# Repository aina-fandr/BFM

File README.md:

# Projet AGV bancaire — BFM V4

Bienvenue dans le dépôt du projet AGV bancaire. Cette page regroupe les liens vers les présentations, les livrables principaux et les dossiers de travail.

## Présentations et livrables principaux

- **[Présentation aux investisseurs — version HTML](<LIVRABLES FINAUX/Dossier de financement/Presentation_investisseurs_AGV_GARP_c.html>)**
- [Dossier de financement — version PDF](<LIVRABLES FINAUX/Dossier de financement/Dossier_financement_AGV.pdf>)
- [Dossier de financement — version HTML](<LIVRABLES FINAUX/Dossier de financement/Dossier_financement_AGV.html>)
- [Présentation visuelle interactive BFM V4](<LIVRABLES FINAUX/Dossier de Conception Final/BFM_V4_GITHUB/index.html>) — modèles 3D, plans et ressources associés
- [Atlas 2D BFM V4](<LIVRABLES FINAUX/Dossier de financement/Atlas_2D_BFM_V4.html>)
- [Simulation AGV hors ligne](<LIVRABLES FINAUX/Dossier de financement/Simulation_AGV_hors_ligne.html>)
- [Étude de la carte électronique](<LIVRABLES FINAUX/Dossier de financement/Etude_PCB_AGV.html>)
- [État des dossiers livrables](<LIVRABLES FINAUX/ETAT_DES_DOSSIERS.md>)

> GitHub affiche parfois les fichiers HTML comme du code dans le dépôt. Pour ouvrir les présentations HTML comme des pages web, activez GitHub Pages dans les paramètres du dépôt. La présentation BFM V4 doit être publiée avec son dossier `assets`.

## Dossiers du projet

| Domaine | Contenu |
|---|---|
| [Approvisionnement](<APPROVISIONNEMENT/README.md>) | Nomenclatures, budgets et achats |
| [Coordination du projet](<COORDINATION DU PROJET/README.md>) | Équipe, réunions et suivi |
| [Électronique](<ELECTRONIQUE/README.md>) | Architecture, alimentation et câblage |
| [Informatique](<INFORMATIQUE/README.md>) | Logiciel, communication et firmware |
| [Livrables finaux](<LIVRABLES FINAUX/README.md>) | Dossiers de conception, fabrication et validation |
| [Mécanique](<MECANIQUE/README.md>) | Études, calculs et modélisation |
| [Qualité et sécurité](<QUALITE ET SECURITE/README.md>) | Risques, normes et validation |
| [Robotique](<ROBOTIQUE/README.md>) | Architecture, cartographie et simulation |
| [Outils](<outils/README.md>) | Scripts et génération de documentation |

## Documentation

- [Avancement du projet](<AVANCEMENT_PROJET.md>)
- [Synthèse détaillée du projet](<README_PROJET.md>)
- [Guide des registres](<README_REGISTRES.md>)
- [Structure complète des fichiers](<STRUCTURE_COMPLETE.md>)

Les modèles, budgets et simulations sont des éléments de conception ou des estimations. Ils ne constituent pas une validation de fabrication, de sécurité ou de performance réelle.

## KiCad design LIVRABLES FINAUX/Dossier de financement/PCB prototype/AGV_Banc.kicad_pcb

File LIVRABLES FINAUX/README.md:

# LIVRABLES FINAUX

Regroupe les dossiers de conception, fabrication, electronique, informatique, robotique, qualite, rapports et validations.

## Contenu du dossier

- [Cahier Des Charges Final/](<Cahier Des Charges Final/>)
- [Dossier de Conception Final/](<Dossier de Conception Final/>)
- [Dossier de Fabrication/](<Dossier de Fabrication/>)
- [Dossier Electrique Final/](<Dossier Electrique Final/>)
- [Dossier Informatique/](<Dossier Informatique/>)
- [Dossier Qualité et Securité/](<Dossier Qualité et Securité/>)
- [Dossier Robotique/](<Dossier Robotique/>)
- [Rapport Final du Projet/](<Rapport Final du Projet/>)
- [Rapports Tests et Validation/](<Rapports Tests et Validation/>)

Fichiers directement presents a la racine :
- `ETAT_DES_DOSSIERS.md`

## Structure complete

Voir [STRUCTURE_COMPLETE.md](<STRUCTURE_COMPLETE.md>) pour l'arborescence detaillee de ce dossier et de ses sous-dossiers.

## Mise a jour

Depuis la racine `PROJET BANQUE CENTRALE`, regenerer les structures avec :

```powershell
python .\outils\generer_documentation_dossiers.py
```

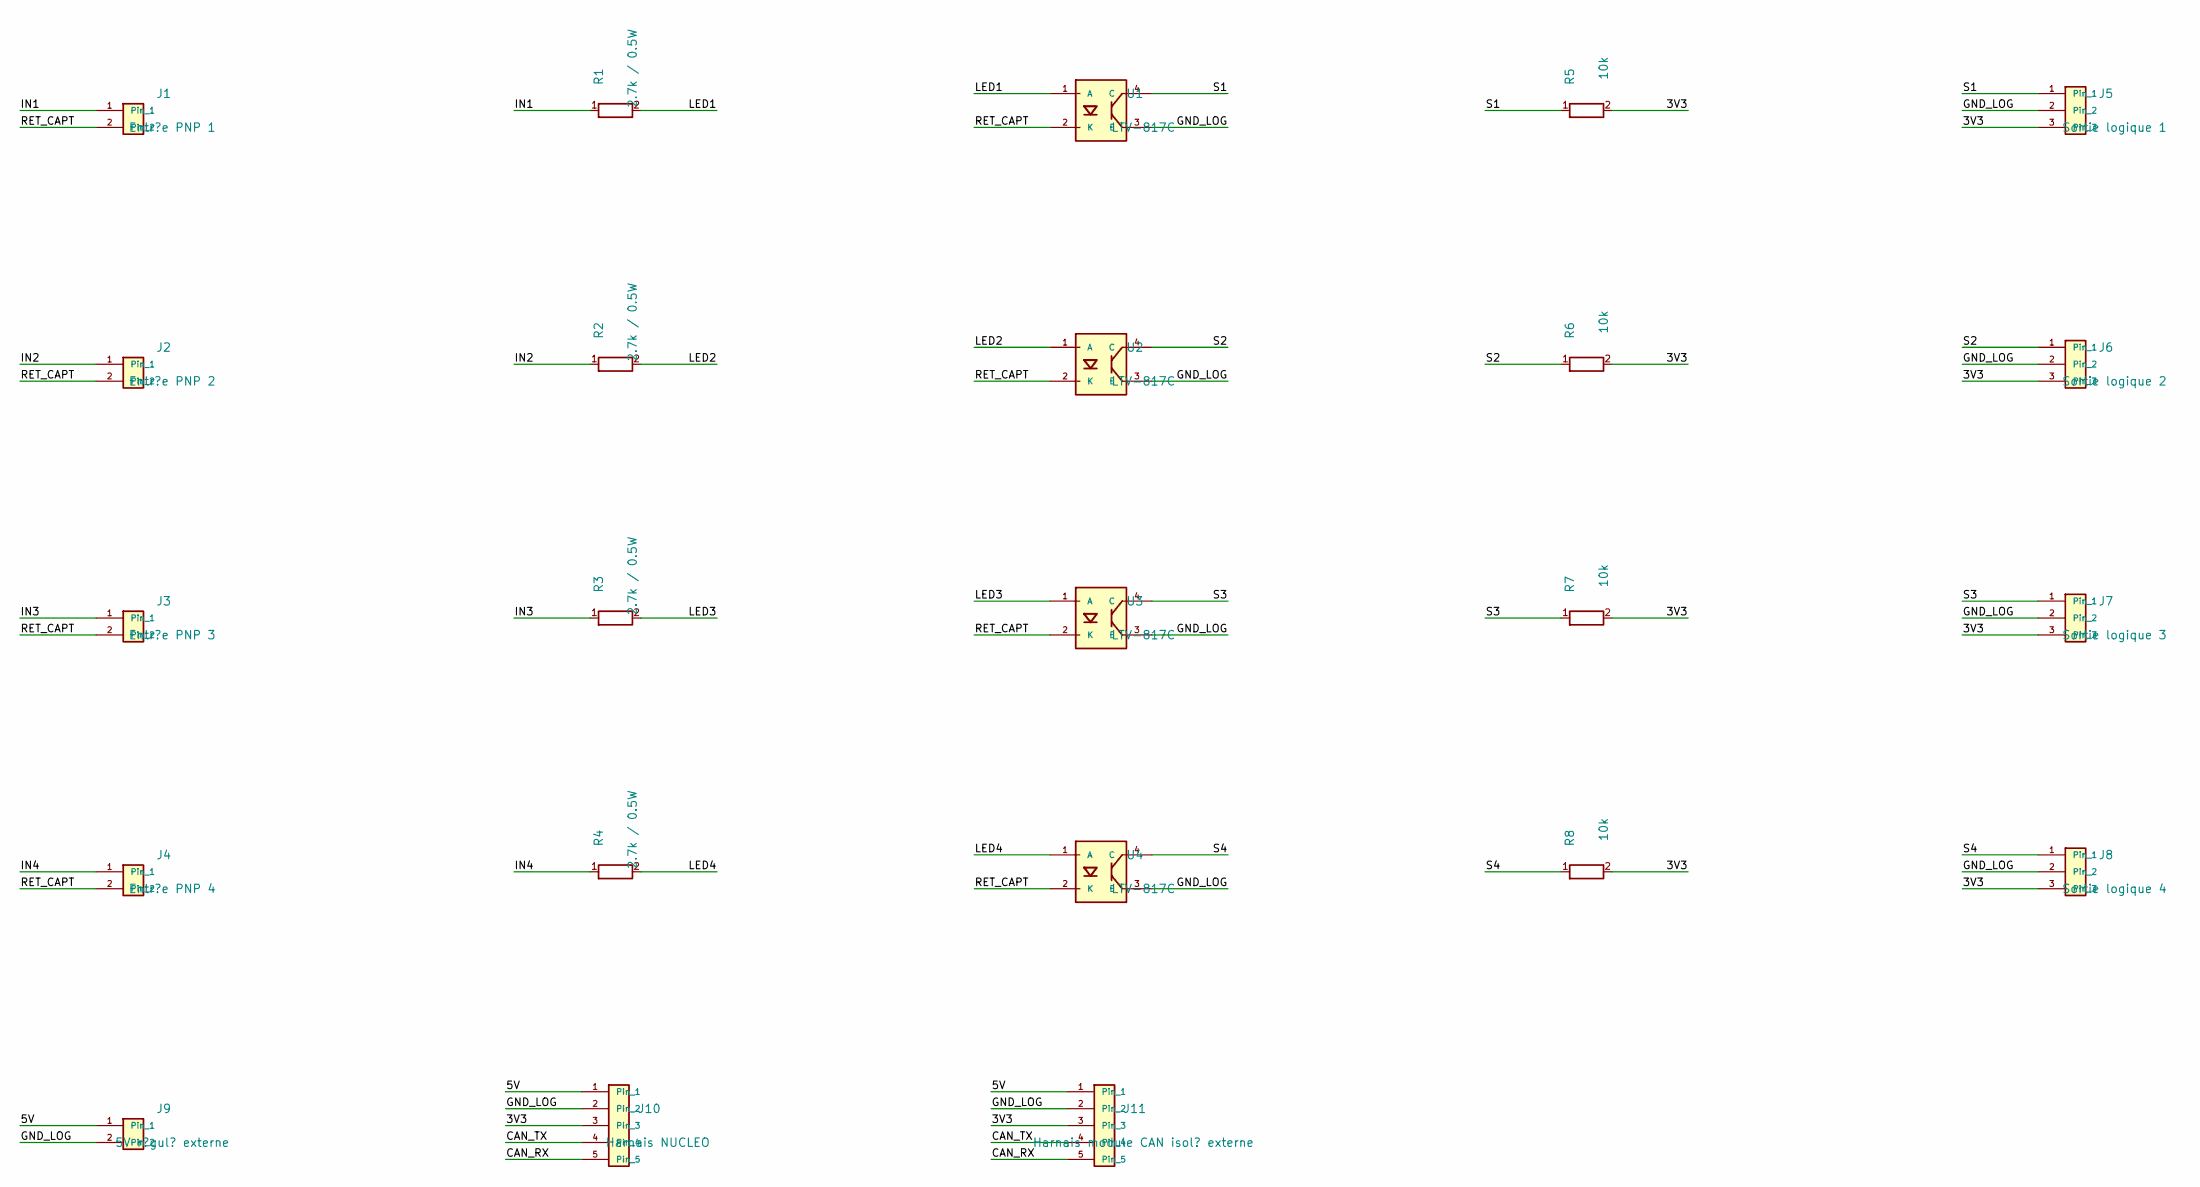
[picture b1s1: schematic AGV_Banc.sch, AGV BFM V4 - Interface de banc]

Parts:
J1: Entr?e PNP 1
J2: Entr?e PNP 2
J3: Entr?e PNP 3
J4: Entr?e PNP 4
J5: Sortie logique 1
J6: Sortie logique 2
J7: Sortie logique 3
J8: Sortie logique 4
J9: 5V r?gul? externe
J10: Harnais NUCLEO
J11: Harnais module CAN isol? externe
R1, R2, R3, R4: 2.7k / 0.5W
R5, R6, R7, R8: 10k
U1, U2, U3, U4: LTV-817C

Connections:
3V3: J5.3, J6.3, J7.3, J8.3, J10.3, J11.3, R5.2, R6.2, R7.2, R8.2
5V: J9.1, J10.1, J11.1
CAN_RX: J10.5, J11.5
CAN_TX: J10.4, J11.4
GND_LOG: J5.2, J6.2, J7.2, J8.2, J9.2, J10.2, J11.2, U1.3 (E), U2.3 (E), U3.3 (E), U4.3 (E)
IN1: J1.1, R1.1
IN2: J2.1, R2.1
IN3: J3.1, R3.1
IN4: J4.1, R4.1
LED1: R1.2, U1.1 (A)
LED2: R2.2, U2.1 (A)
LED3: R3.2, U3.1 (A)
LED4: R4.2, U4.1 (A)
RET_CAPT: J1.2, J2.2, J3.2, J4.2, U1.2 (K), U2.2 (K), U3.2 (K), U4.2 (K)
S1: J5.1, R5.1, U1.4 (C)
S2: J6.1, R6.1, U2.4 (C)
S3: J7.1, R7.1, U3.4 (C)
S4: J8.1, R8.1, U4.4 (C)

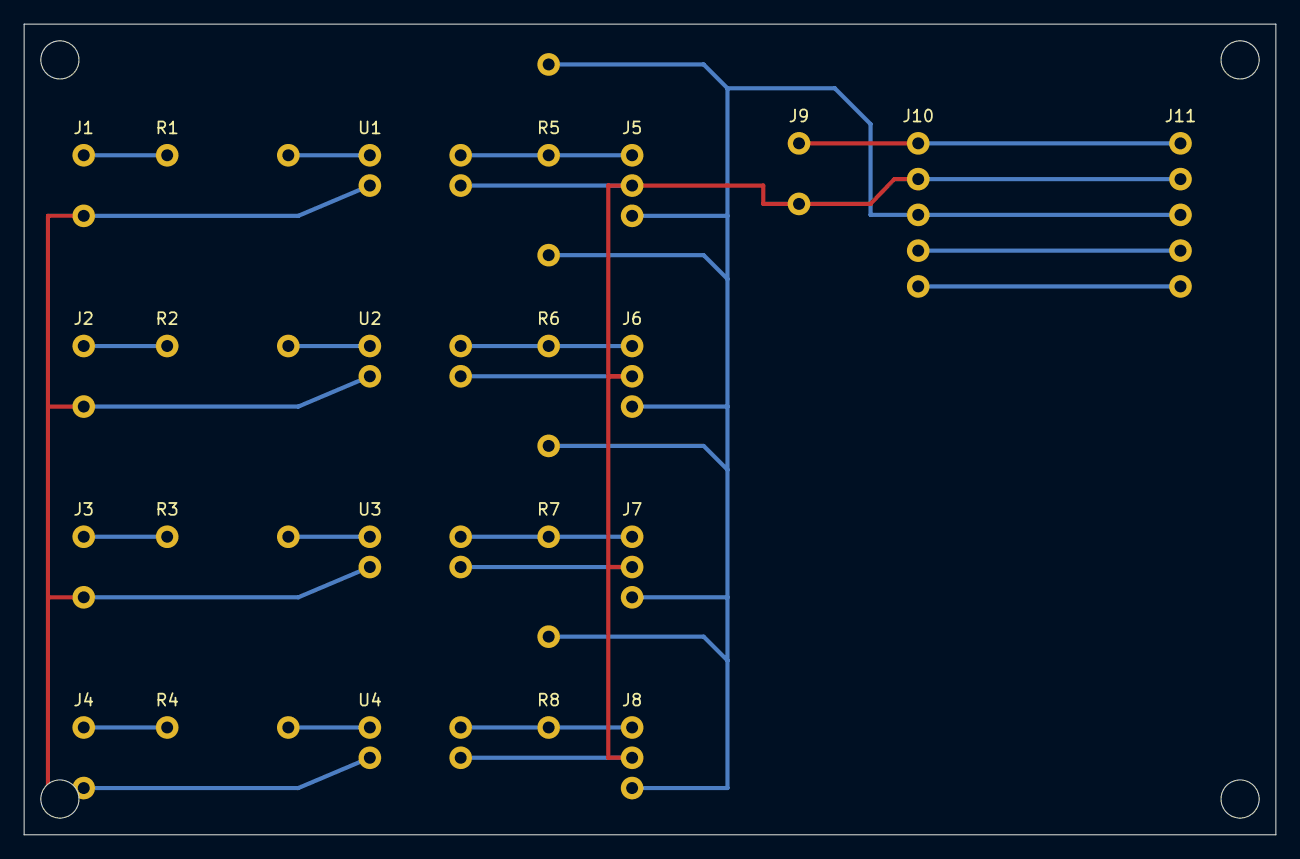
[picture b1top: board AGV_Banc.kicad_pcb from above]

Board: 2 copper layers, 105.0 x 68.0 mm, 23 parts (0 on the bottom side), 18 nets.
